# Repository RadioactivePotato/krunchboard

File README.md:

# NO LONGER UPDATE, CHECK OUT A NEWER VERSION [HERE](https://github.com/krunchiekrunch/krunchboard-90)

# krunchboard
A custom 80% ISO mechanical keyboard powered by a Raspberry Pi Pico with KMK

# Note

Prod V1 of the PCB has its I2C lines flipped for the 0.91" OLED Display and MCP23017

Firmware doesn't work yet

# About
I made this keyboard after I designed my [macropad](https://github.com/krunchiekrunch/krunchpad), and I thought this would be a fun project to do, I've also never owned a mechanical keyboard so maybe this is a good way to start?

# Images

| PCB | 3D View |
|-----|------------|
|  |  |
|  |  |

# Render

# BOM
| Qty | Item                               | Notes                                     | Cost (USD) | URL                                                                                                         |
|-----|------------------------------------|-------------------------------------------|------------|-------------------------------------------------------------------------------------------------------------|
| 1   | Raspberry Pi Pico                  | USB-C Clone                               | 2.30       | [AliExpress](https://www.aliexpress.com/item/1005006067365069.html)                                         |
| 1   | EC11 Rotary Encoder                |                                           | 2.54       | [AliExpress](https://www.aliexpress.com/item/1005008413622715.html)                                         |
| 1   | Rotary Encoder Knob                |                                           | 0.98       | [AliExpress](https://www.aliexpress.com/item/1005007951780072.html)                                         |
| 92  | Kailh MX Hotswap Socket            | Hotswapping for switches                  | 7.88       | [AliExpress](https://www.aliexpress.com/item/1005007476614771.html)                                         |
| 1   | 0.91" OLED Display                 |                                           | 2.06       | [AliExpress](https://www.aliexpress.com/item/1005007672413060.html)                                         |
| 1   | 0.96" OLED Display                 |                                           | 2.18       | [AliExpress](https://www.aliexpress.com/item/1005006985022252.html)                                         |
| 1   | MX Stabilisers Set                 | For big keycaps                           | 4.37       | [AliExpress](https://www.aliexpress.com/item/1005009345248282.html)                                         |
| 93  | 1N4148W Diode (SOD-123)            | Already have                              | 0.50       | [LCSC](https://www.lcsc.com/product-detail/C42441811.html)                                                  |
| 1   | MCP23017 GPIO Expander (SOIC-28)   | Already have                              | 1.94       | [LCSC](https://www.lcsc.com/product-detail/C629440.html)                                                    |
| 2   | 4 Slot 2.54mm Socket               | Already have                              | 0.43       | [LCSC](https://www.lcsc.com/product-detail/C7509546.html)                                                   |
| 6   | SK6812MINI-E / SK6812E Neopixel    | Already have                              | 0.74       | [LCSC](https://www.lcsc.com/product-detail/C5149201.html)                                                   |
|     |                                    |                                           |            |                                                                                                             |
| 1   | Keycaps Set                        |                                           | 13.94      | [AliExpress](https://www.aliexpress.com/item/1005009177442825.html)                                         |
| 87  | Linear Key Switch                  | Main keyboard switches                    | 9.31       | [AliExpress](https://www.aliexpress.com/item/1005002378701948.html)                                         |
| 5   | Tactile MX-Style Switch            | Shortcut keys switches                    | 2.00       | [AliExpress](https://www.aliexpress.com/item/1005009249474760.html)                                         |
| 6   | Sticky rubber feet                 | Antislip for keyboard                     | 1.26       | [AliExpress](https://www.aliexpress.com/item/1005006832476105.html)                                         |
|     |                                    |                                           |            |                                                                                                             |
| 12  | M3x5mmx4mm Heatset Inserts (W\*H)  | For mounting                              | 2.13       | [AliExpress](https://www.aliexpress.com/item/1005007640664497.html)                                         |
| 12  | M3x5mm Screws                      | For case assembly                         | 2.44       | [AliExpress](https://www.aliexpress.com/item/1005006621501802.html)                                         |
|     |                                    |                                           |            |                                                                                                             |
| 1   | Solder Paste                       | Reflow soldering for SMD                  | 5.11       | [AliExpress](https://www.aliexpress.com/item/1005009377104599.htm)                                          |
| 1   | Solder Wire                        | 50g                                       | 3.32       | [AliExpress](https://www.aliexpress.com/item/1005008053204920.html)                                         |
|     |                                    |                                           |            |                                                                                                             |
| 1   | 3D Printed Case                    | print-legion postage (via royal mail)     | 7.00       | print-legion                                                                                                |
| 1   | PCB                                | Shipping $12.89                           | 41.79      | JLCPCB                                                                                                      |
|     |                                    |                                           |            |                                                                                                             |
|     |                                    | **Total AliExpress (GBP)**                | **61.82**  |                                                                                                             |
|     |                                    | **PCB and Case (GBP)**                    | **48.79**  |                                                                                                             |
|     |                                    | Total (USD)**                             | **103.61** |                                                                                                             |

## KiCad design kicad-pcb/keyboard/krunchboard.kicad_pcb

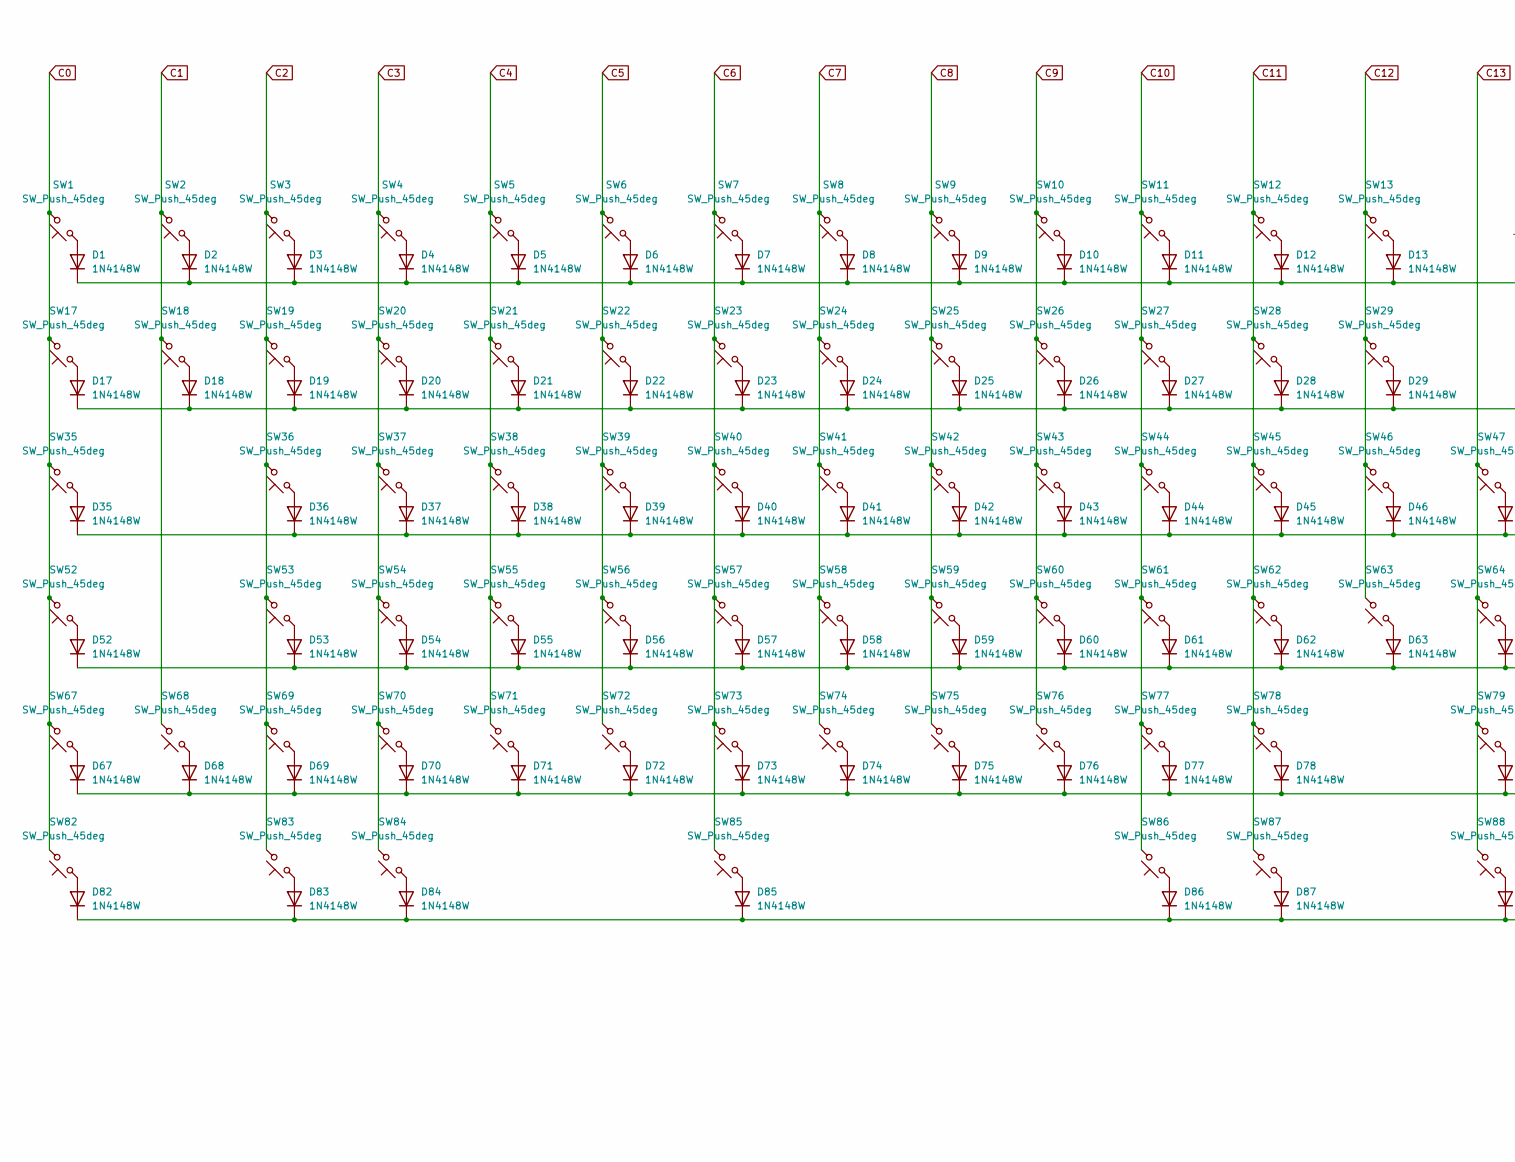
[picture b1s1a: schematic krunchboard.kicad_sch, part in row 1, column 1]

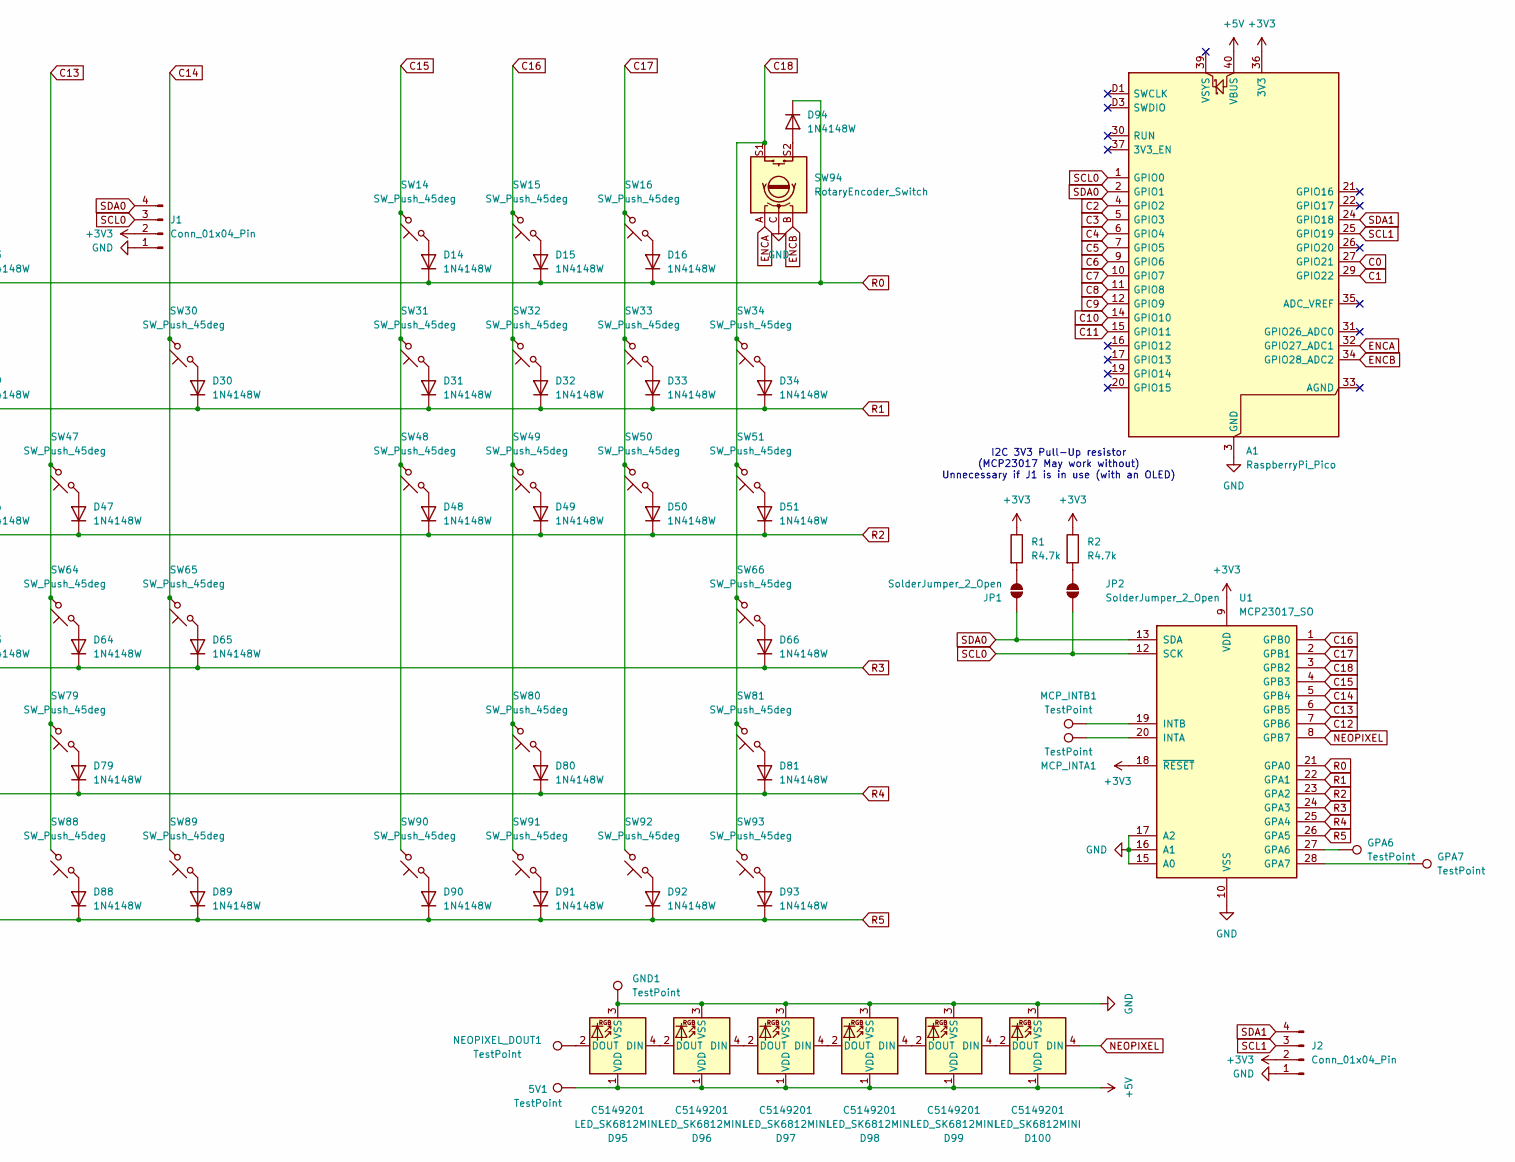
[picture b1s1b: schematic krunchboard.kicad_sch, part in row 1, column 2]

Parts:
5V1: TestPoint; TestPoint_Pad_D2.5mm
A1: RaspberryPi_Pico; RaspberryPi_Pico_SMD_HandSolder
D1, D2, D3, D4, D5, D6, D7, D8, D9, D10, D11, D12, D13, D14, D15, D16, D17, D18, D19, D20, D21, D22, D23, D24, D25, D26, D27, D28, D29, D30, D31, D32, D33, D34, D35, D36, D37, D38, D39, D40, D41, D42, D43, D44, D45, D46, D47, D48, D49, D50, D51, D52, D53, D54, D55, D56, D57, D58, D59, D60, D61, D62, D63, D64, D65, D66, D67, D68, D69, D70, D71, D72, D73, D74, D75, D76, D77, D78, D79, D80, D81, D82, D83, D84, D85, D86, D87, D88, D89, D90, D91, D92, D93, D94: 1N4148W; D_SOD-123
D95, D96, D97, D98, D99, D100: LED_SK6812MINI; SK6812-MINI-E; LCSC C5149201
GND1: TestPoint; TestPoint_Pad_D2.5mm
GPA6, GPA7: TestPoint; TestPoint_Pad_D2.5mm
J1, J2: Conn_01x04_Pin; PinSocket_1x04_P2.54mm_Vertical
JP1, JP2: SolderJumper_2_Open; SolderJumper-2_P1.3mm_Open_TrianglePad1.0x1.5mm
MCP_INTA1: TestPoint; TestPoint_Pad_D2.5mm
MCP_INTB1: TestPoint; TestPoint_Pad_D2.5mm
NEOPIXEL_DOUT1: TestPoint; TestPoint_Pad_D2.5mm
R1, R2: R4.7k; R_0805_2012Metric_Pad1.20x1.40mm_HandSolder
SW1, SW2, SW3, SW4, SW5, SW6, SW7, SW8, SW9, SW10, SW11, SW12, SW13, SW14, SW15, SW16, SW17, SW18, SW19, SW20, SW21, SW22, SW23, SW24, SW25, SW26, SW27, SW28, SW29, SW31, SW32, SW33, SW34, SW36, SW37, SW38, SW39, SW40, SW41, SW42, SW43, SW44, SW45, SW46, SW47, SW48, SW49, SW50, SW51, SW53, SW54, SW55, SW56, SW57, SW58, SW59, SW60, SW61, SW62, SW63, SW64, SW66, SW68, SW69, SW70, SW71, SW72, SW73, SW74, SW75, SW76, SW77, SW78, SW80, SW81, SW90, SW91, SW92, SW93: SW_Push_45deg; Hotswap_MX_Plated_1.00u
SW30: SW_Push_45deg; Hotswap_MX_Plated_2.00u
SW35: SW_Push_45deg; Hotswap_MX_Plated_1.50u
SW52: SW_Push_45deg; Hotswap_MX_Plated_1.75u
SW65: SW_Push_45deg; Hotswap_MX_Plated_ISOEnter
SW67, SW82, SW83, SW84, SW86, SW87, SW88, SW89: SW_Push_45deg; Hotswap_MX_Plated_1.25u
SW79: SW_Push_45deg; Hotswap_MX_Plated_2.75u
SW85: SW_Push_45deg; Hotswap_MX_Plated_6.25u
SW94: RotaryEncoder_Switch; RotaryEncoder_Alps_EC11E-Switch_Vertical_H20mm
U1: MCP23017_SO; SOIC-28W_7.5x17.9mm_P1.27mm

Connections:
+3V3: A1.36 (3V3), J1.2, J2.2, R1.1, R2.1, U1.9 (VDD), U1.18 (~RESET)
+5V: 5V1.1, A1.40 (VBUS), D95.1 (VDD), D96.1 (VDD), D97.1 (VDD), D98.1 (VDD), D99.1 (VDD), D100.1 (VDD)
C0: A1.27 (GPIO21), SW1.2, SW17.2, SW35.2, SW52.2, SW67.2, SW82.2
C1: A1.29 (GPIO22), SW2.2, SW18.2, SW68.2
C2: A1.4 (GPIO2), SW3.2, SW19.2, SW36.2, SW53.2, SW69.2, SW83.2
C3: A1.5 (GPIO3), SW4.2, SW20.2, SW37.2, SW54.2, SW70.2, SW84.2
C4: A1.6 (GPIO4), SW5.2, SW21.2, SW38.2, SW55.2, SW71.2
C5: A1.7 (GPIO5), SW6.2, SW22.2, SW39.2, SW56.2, SW72.2
C6: A1.9 (GPIO6), SW7.2, SW23.2, SW40.2, SW57.2, SW73.2, SW85.2
C7: A1.10 (GPIO7), SW8.2, SW24.2, SW41.2, SW58.2, SW74.2
C8: A1.11 (GPIO8), SW9.2, SW25.2, SW42.2, SW59.2, SW75.2
C9: A1.12 (GPIO9), SW10.2, SW26.2, SW43.2, SW60.2, SW76.2
C10: A1.14 (GPIO10), SW11.2, SW27.2, SW44.2, SW61.2, SW77.2, SW86.2
C11: A1.15 (GPIO11), SW12.2, SW28.2, SW45.2, SW62.2, SW78.2, SW87.2
C12: SW13.2, SW29.2, SW46.2, SW63.2, U1.7 (GPB6)
C13: SW47.2, SW64.2, SW79.2, SW88.2, U1.6 (GPB5)
C14: SW30.2, SW65.2, SW89.2, U1.5 (GPB4)
C15: SW14.2, SW31.2, SW48.2, SW90.2, U1.4 (GPB3)
C16: SW15.2, SW32.2, SW49.2, SW80.2, SW91.2, U1.1 (GPB0)
C17: SW16.2, SW33.2, SW50.2, SW92.2, U1.2 (GPB1)
C18: SW34.2, SW51.2, SW66.2, SW81.2, SW93.2, SW94.S1, U1.3 (GPB2)
ENCA: A1.32 (GPIO27_ADC1), SW94.A
ENCB: A1.34 (GPIO28_ADC2), SW94.B
GND: A1.3 (GND), A1.8 (GND), A1.13 (GND), A1.18 (GND), A1.23 (GND), A1.28 (GND), A1.38 (GND), A1.D2 (GND), D95.3 (VSS), D96.3 (VSS), D97.3 (VSS), D98.3 (VSS), D99.3 (VSS), D100.3 (VSS), GND1.1, J1.1, J2.1, SW94.C, U1.10 (VSS), U1.15 (A0), U1.16 (A1), U1.17 (A2)
NEOPIXEL: D100.4 (DIN), U1.8 (GPB7)
unnamed: D1.2 (A), SW1.1
unnamed: D2.2 (A), SW2.1
unnamed: D3.2 (A), SW3.1
unnamed: D4.2 (A), SW4.1
unnamed: D5.2 (A), SW5.1
unnamed: D6.2 (A), SW6.1
unnamed: D7.2 (A), SW7.1
unnamed: D8.2 (A), SW8.1
unnamed: D9.2 (A), SW9.1
unnamed: D10.2 (A), SW10.1
unnamed: D11.2 (A), SW11.1
unnamed: D12.2 (A), SW12.1
unnamed: D13.2 (A), SW13.1
unnamed: D14.2 (A), SW14.1
unnamed: D15.2 (A), SW15.1
unnamed: D16.2 (A), SW16.1
unnamed: D17.2 (A), SW17.1
unnamed: D18.2 (A), SW18.1
unnamed: D19.2 (A), SW19.1
unnamed: D20.2 (A), SW20.1
unnamed: D21.2 (A), SW21.1
unnamed: D22.2 (A), SW22.1
unnamed: D23.2 (A), SW23.1
unnamed: D24.2 (A), SW24.1
unnamed: D25.2 (A), SW25.1
unnamed: D26.2 (A), SW26.1
unnamed: D27.2 (A), SW27.1
unnamed: D28.2 (A), SW28.1
unnamed: D29.2 (A), SW29.1
unnamed: D30.2 (A), SW30.1
unnamed: D31.2 (A), SW31.1
unnamed: D32.2 (A), SW32.1
unnamed: D33.2 (A), SW33.1
unnamed: D34.2 (A), SW34.1
unnamed: D35.2 (A), SW35.1
unnamed: D36.2 (A), SW36.1
unnamed: D37.2 (A), SW37.1
unnamed: D38.2 (A), SW38.1
unnamed: D39.2 (A), SW39.1
unnamed: D40.2 (A), SW40.1
unnamed: D41.2 (A), SW41.1
unnamed: D42.2 (A), SW42.1
unnamed: D43.2 (A), SW43.1
unnamed: D44.2 (A), SW44.1
unnamed: D45.2 (A), SW45.1
unnamed: D46.2 (A), SW46.1
unnamed: D47.2 (A), SW47.1
unnamed: D48.2 (A), SW48.1
unnamed: D49.2 (A), SW49.1
unnamed: D50.2 (A), SW50.1
unnamed: D51.2 (A), SW51.1
unnamed: D52.2 (A), SW52.1
unnamed: D53.2 (A), SW53.1
unnamed: D54.2 (A), SW54.1
unnamed: D55.2 (A), SW55.1
unnamed: D56.2 (A), SW56.1
unnamed: D57.2 (A), SW57.1
unnamed: D58.2 (A), SW58.1
unnamed: D59.2 (A), SW59.1
unnamed: D60.2 (A), SW60.1
unnamed: D61.2 (A), SW61.1
unnamed: D62.2 (A), SW62.1
unnamed: D63.2 (A), SW63.1
unnamed: D64.2 (A), SW64.1
unnamed: D65.2 (A), SW65.1
unnamed: D66.2 (A), SW66.1
unnamed: D67.2 (A), SW67.1
unnamed: D68.2 (A), SW68.1
unnamed: D69.2 (A), SW69.1
unnamed: D70.2 (A), SW70.1
unnamed: D71.2 (A), SW71.1
unnamed: D72.2 (A), SW72.1
unnamed: D73.2 (A), SW73.1
unnamed: D74.2 (A), SW74.1
unnamed: D75.2 (A), SW75.1
unnamed: D76.2 (A), SW76.1
unnamed: D77.2 (A), SW77.1
unnamed: D78.2 (A), SW78.1
unnamed: D79.2 (A), SW79.1
unnamed: D80.2 (A), SW80.1
unnamed: D81.2 (A), SW81.1
unnamed: D82.2 (A), SW82.1
unnamed: D83.2 (A), SW83.1
unnamed: D84.2 (A), SW84.1
unnamed: D85.2 (A), SW85.1
unnamed: D86.2 (A), SW86.1
unnamed: D87.2 (A), SW87.1
unnamed: D88.2 (A), SW88.1
unnamed: D89.2 (A), SW89.1
unnamed: D90.2 (A), SW90.1
unnamed: D91.2 (A), SW91.1
unnamed: D92.2 (A), SW92.1
unnamed: D93.2 (A), SW93.1
unnamed: D94.2 (A), SW94.S2
unnamed: D95.4 (DIN), D96.2 (DOUT)
unnamed: D95.2 (DOUT), NEOPIXEL_DOUT1.1
unnamed: D96.4 (DIN), D97.2 (DOUT)
unnamed: D97.4 (DIN), D98.2 (DOUT)
unnamed: D98.4 (DIN), D99.2 (DOUT)
unnamed: D99.4 (DIN), D100.2 (DOUT)
unnamed: JP1.1 (A), R1.2
unnamed: JP2.1 (A), R2.2
unnamed: GPA6.1, U1.27 (GPA6)
unnamed: GPA7.1, U1.28 (GPA7)
unnamed: MCP_INTA1.1, U1.20 (INTA)
unnamed: MCP_INTB1.1, U1.19 (INTB)
R0: D1.1 (K), D2.1 (K), D3.1 (K), D4.1 (K), D5.1 (K), D6.1 (K), D7.1 (K), D8.1 (K), D9.1 (K), D10.1 (K), D11.1 (K), D12.1 (K), D13.1 (K), D14.1 (K), D15.1 (K), D16.1 (K), D94.1 (K), U1.21 (GPA0)
R1: D17.1 (K), D18.1 (K), D19.1 (K), D20.1 (K), D21.1 (K), D22.1 (K), D23.1 (K), D24.1 (K), D25.1 (K), D26.1 (K), D27.1 (K), D28.1 (K), D29.1 (K), D30.1 (K), D31.1 (K), D32.1 (K), D33.1 (K), D34.1 (K), U1.22 (GPA1)
R2: D35.1 (K), D36.1 (K), D37.1 (K), D38.1 (K), D39.1 (K), D40.1 (K), D41.1 (K), D42.1 (K), D43.1 (K), D44.1 (K), D45.1 (K), D46.1 (K), D47.1 (K), D48.1 (K), D49.1 (K), D50.1 (K), D51.1 (K), U1.23 (GPA2)
R3: D52.1 (K), D53.1 (K), D54.1 (K), D55.1 (K), D56.1 (K), D57.1 (K), D58.1 (K), D59.1 (K), D60.1 (K), D61.1 (K), D62.1 (K), D63.1 (K), D64.1 (K), D65.1 (K), D66.1 (K), U1.24 (GPA3)
R4: D67.1 (K), D68.1 (K), D69.1 (K), D70.1 (K), D71.1 (K), D72.1 (K), D73.1 (K), D74.1 (K), D75.1 (K), D76.1 (K), D77.1 (K), D78.1 (K), D79.1 (K), D80.1 (K), D81.1 (K), U1.25 (GPA4)
R5: D82.1 (K), D83.1 (K), D84.1 (K), D85.1 (K), D86.1 (K), D87.1 (K), D88.1 (K), D89.1 (K), D90.1 (K), D91.1 (K), D92.1 (K), D93.1 (K), U1.26 (GPA5)
SCL0: A1.1 (GPIO0), J1.3, JP2.2 (B), U1.12 (SCK)
SCL1: A1.25 (GPIO19), J2.3
SDA0: A1.2 (GPIO1), J1.4, JP1.2 (B), U1.13 (SDA)
SDA1: A1.24 (GPIO18), J2.4

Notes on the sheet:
I2C 3V3 Pull-Up resistor (MCP23017 May work without) Unnecessary if J1 is in use (with an OLED)

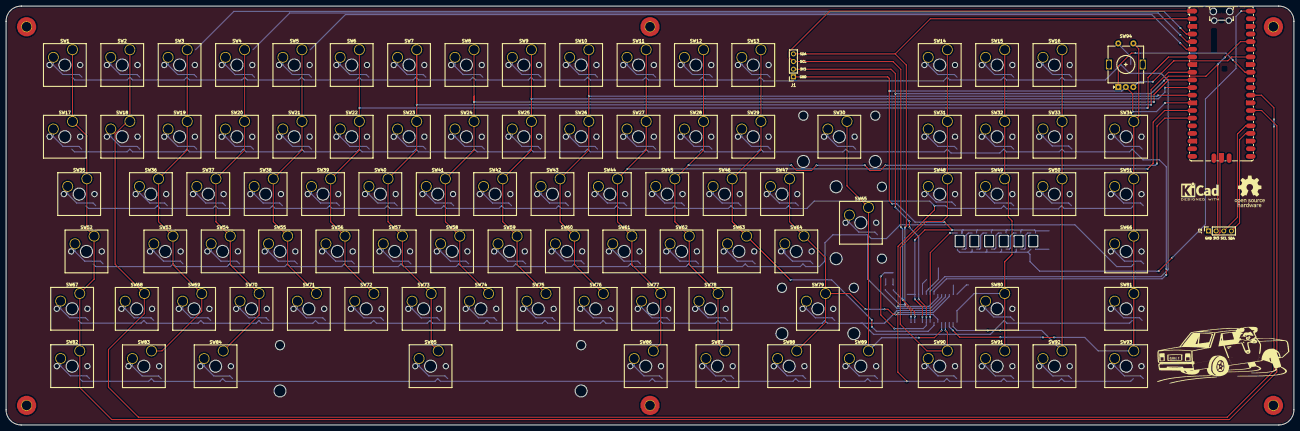
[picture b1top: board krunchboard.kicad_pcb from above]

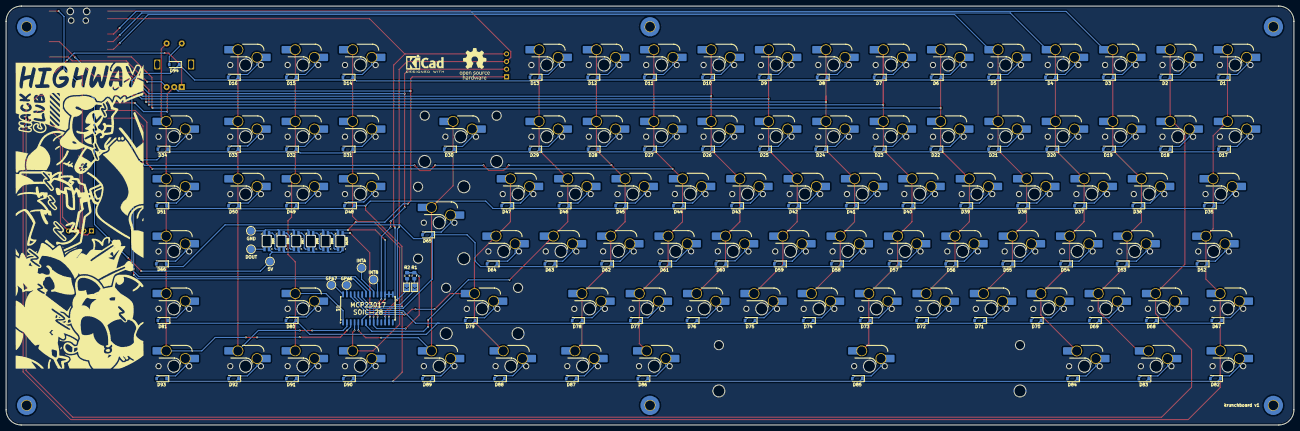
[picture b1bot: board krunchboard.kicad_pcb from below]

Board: 2 copper layers, 427.6 x 139.1 mm, 211 parts (113 on the bottom side), 141 nets.

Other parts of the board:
logo1, logo1#2: KiCad-Logo2_5mm_SilkScreen

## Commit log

2025-06-27 june 27
2025-06-28 june 28
2025-06-30 june 30
2025-07-08 june 8-9
2025-07-09 july 9
2025-07-10 Fixed BOM broken URL
2025-07-10 cad+pcb files / repo setup / assets
2025-07-10 bom update
2025-07-10 switched some items from amazon to aliexpress
2025-07-10 Update total cost
2025-07-10 splitted case in half
2025-07-10 readme images
2025-07-10 readme formatting for images + case image
2025-07-10 plate files
2025-07-10 replaced the half cases and added neopixel to bom
2025-07-10 updated plate files
2025-07-10 Added PCB to BOM
2025-07-10 edited the plate
2025-07-10 even more plate updates
2025-07-10 july 10
2025-07-11 Replaced the pi pico with a usbc clone
2025-07-11 FIRMWARE!!
2025-07-11 added neopixel functions, and moved pinouts
2025-07-11 pcb files, photos, and added 0.96 oled to firmware
2025-07-11 the END?
2025-07-11 data
2025-07-11 about
2025-07-11 bill's csv
2025-07-11 updated bom pricing
2025-07-12 new bill's csv
2025-07-12 swapped 0.96 oled power pins to [GND,VCC,SCL,SDA]
2025-07-16 updated images to use relative dirs
2025-07-22 replaced pin sockets with smd version
2025-07-30 switched mounting styles, updated pcb, plate, and case
2025-07-30 updated 1x04 2.54mm socket url in bom
2025-07-30 updated bom error
2025-08-04 updated images
2025-08-05 assets/render2.png
2025-08-05 case v1.2, added 3d models to pcb, adjusted plate
2025-08-16 case v1.3
2025-08-27 BOM price update
2025-08-27 aug 16 journal
2025-08-27 changed solder paste source
2025-09-04 updated pcb - switched oled socket from smd to tht, added hole for tht socket in case, adjusted pcb vias and silkscreen, added testpoints to pcb
2025-09-13 final v1 pcb revision, plate update
2025-09-25 updated schem, pcb, 3d images
2025-10-04 updated account username
2026-04-22 Update README to direct users to newer version
